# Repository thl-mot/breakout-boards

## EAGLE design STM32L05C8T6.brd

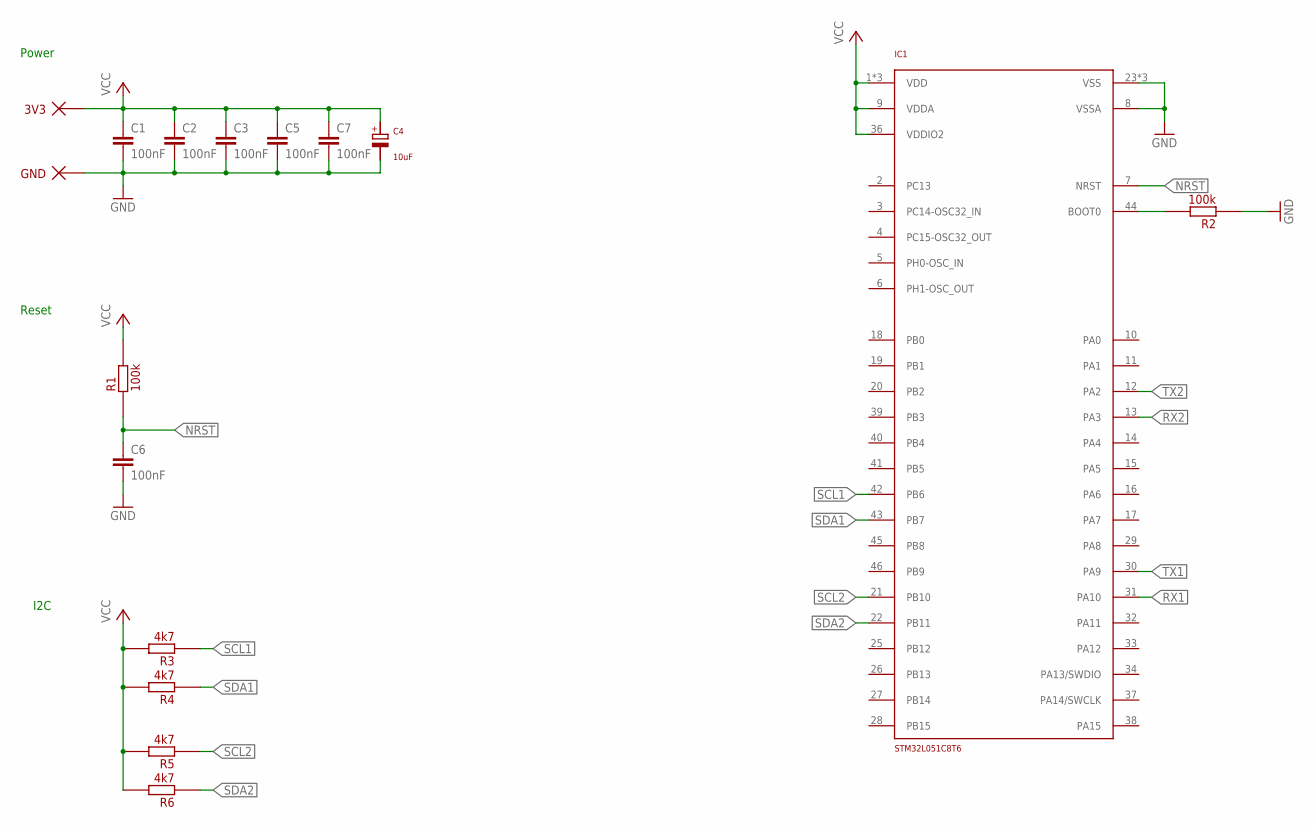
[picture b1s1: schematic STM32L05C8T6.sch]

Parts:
C1, C2, C3, C5, C6, C7: 100nF; C1206
C4: 10uF; SANYO-OSCON_SMD_A5
IC1: STM32L051C8T6; TQFP48_7X7
P1: 3V3; PIN
P2: GND; PIN
R1, R2: 100k; R0603
R3, R4, R5, R6: 4k7; R0603

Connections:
GND: C1.2, C2.2, C3.2, C4.-, C5.2, C6.2, C7.2, IC1.8 (VSSA), IC1.23 (VSS), IC1.35 (VSS), IC1.47 (VSS), P2.P$1, R2.1
unnamed: IC1.44 (BOOT0), R2.2
NRST: C6.1, IC1.7 (NRST), R1.1
RX1: IC1.31 (PA10)
RX2: IC1.13 (PA3)
SCL1: IC1.42 (PB6), R3.1
SCL2: IC1.21 (PB10), R5.1
SDA1: IC1.43 (PB7), R4.1
SDA2: IC1.22 (PB11), R6.1
TX1: IC1.30 (PA9)
TX2: IC1.12 (PA2)
VCC: C1.1, C2.1, C3.1, C4.+, C5.1, C7.1, IC1.1 (VDD), IC1.9 (VDDA), IC1.24 (VDD), IC1.36 (VDDIO2), IC1.48 (VDD), P1.P$1, R1.2, R3.2, R4.2, R5.2, R6.2

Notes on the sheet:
Power
Reset
I2C

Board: 2 copper layers, 20 parts (0 on the bottom side), 8 nets, no tracks yet.

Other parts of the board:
U$1, U$2, U$3, U$4: BOHRUNG_3MM_UNTERLEGSCHEIBE
